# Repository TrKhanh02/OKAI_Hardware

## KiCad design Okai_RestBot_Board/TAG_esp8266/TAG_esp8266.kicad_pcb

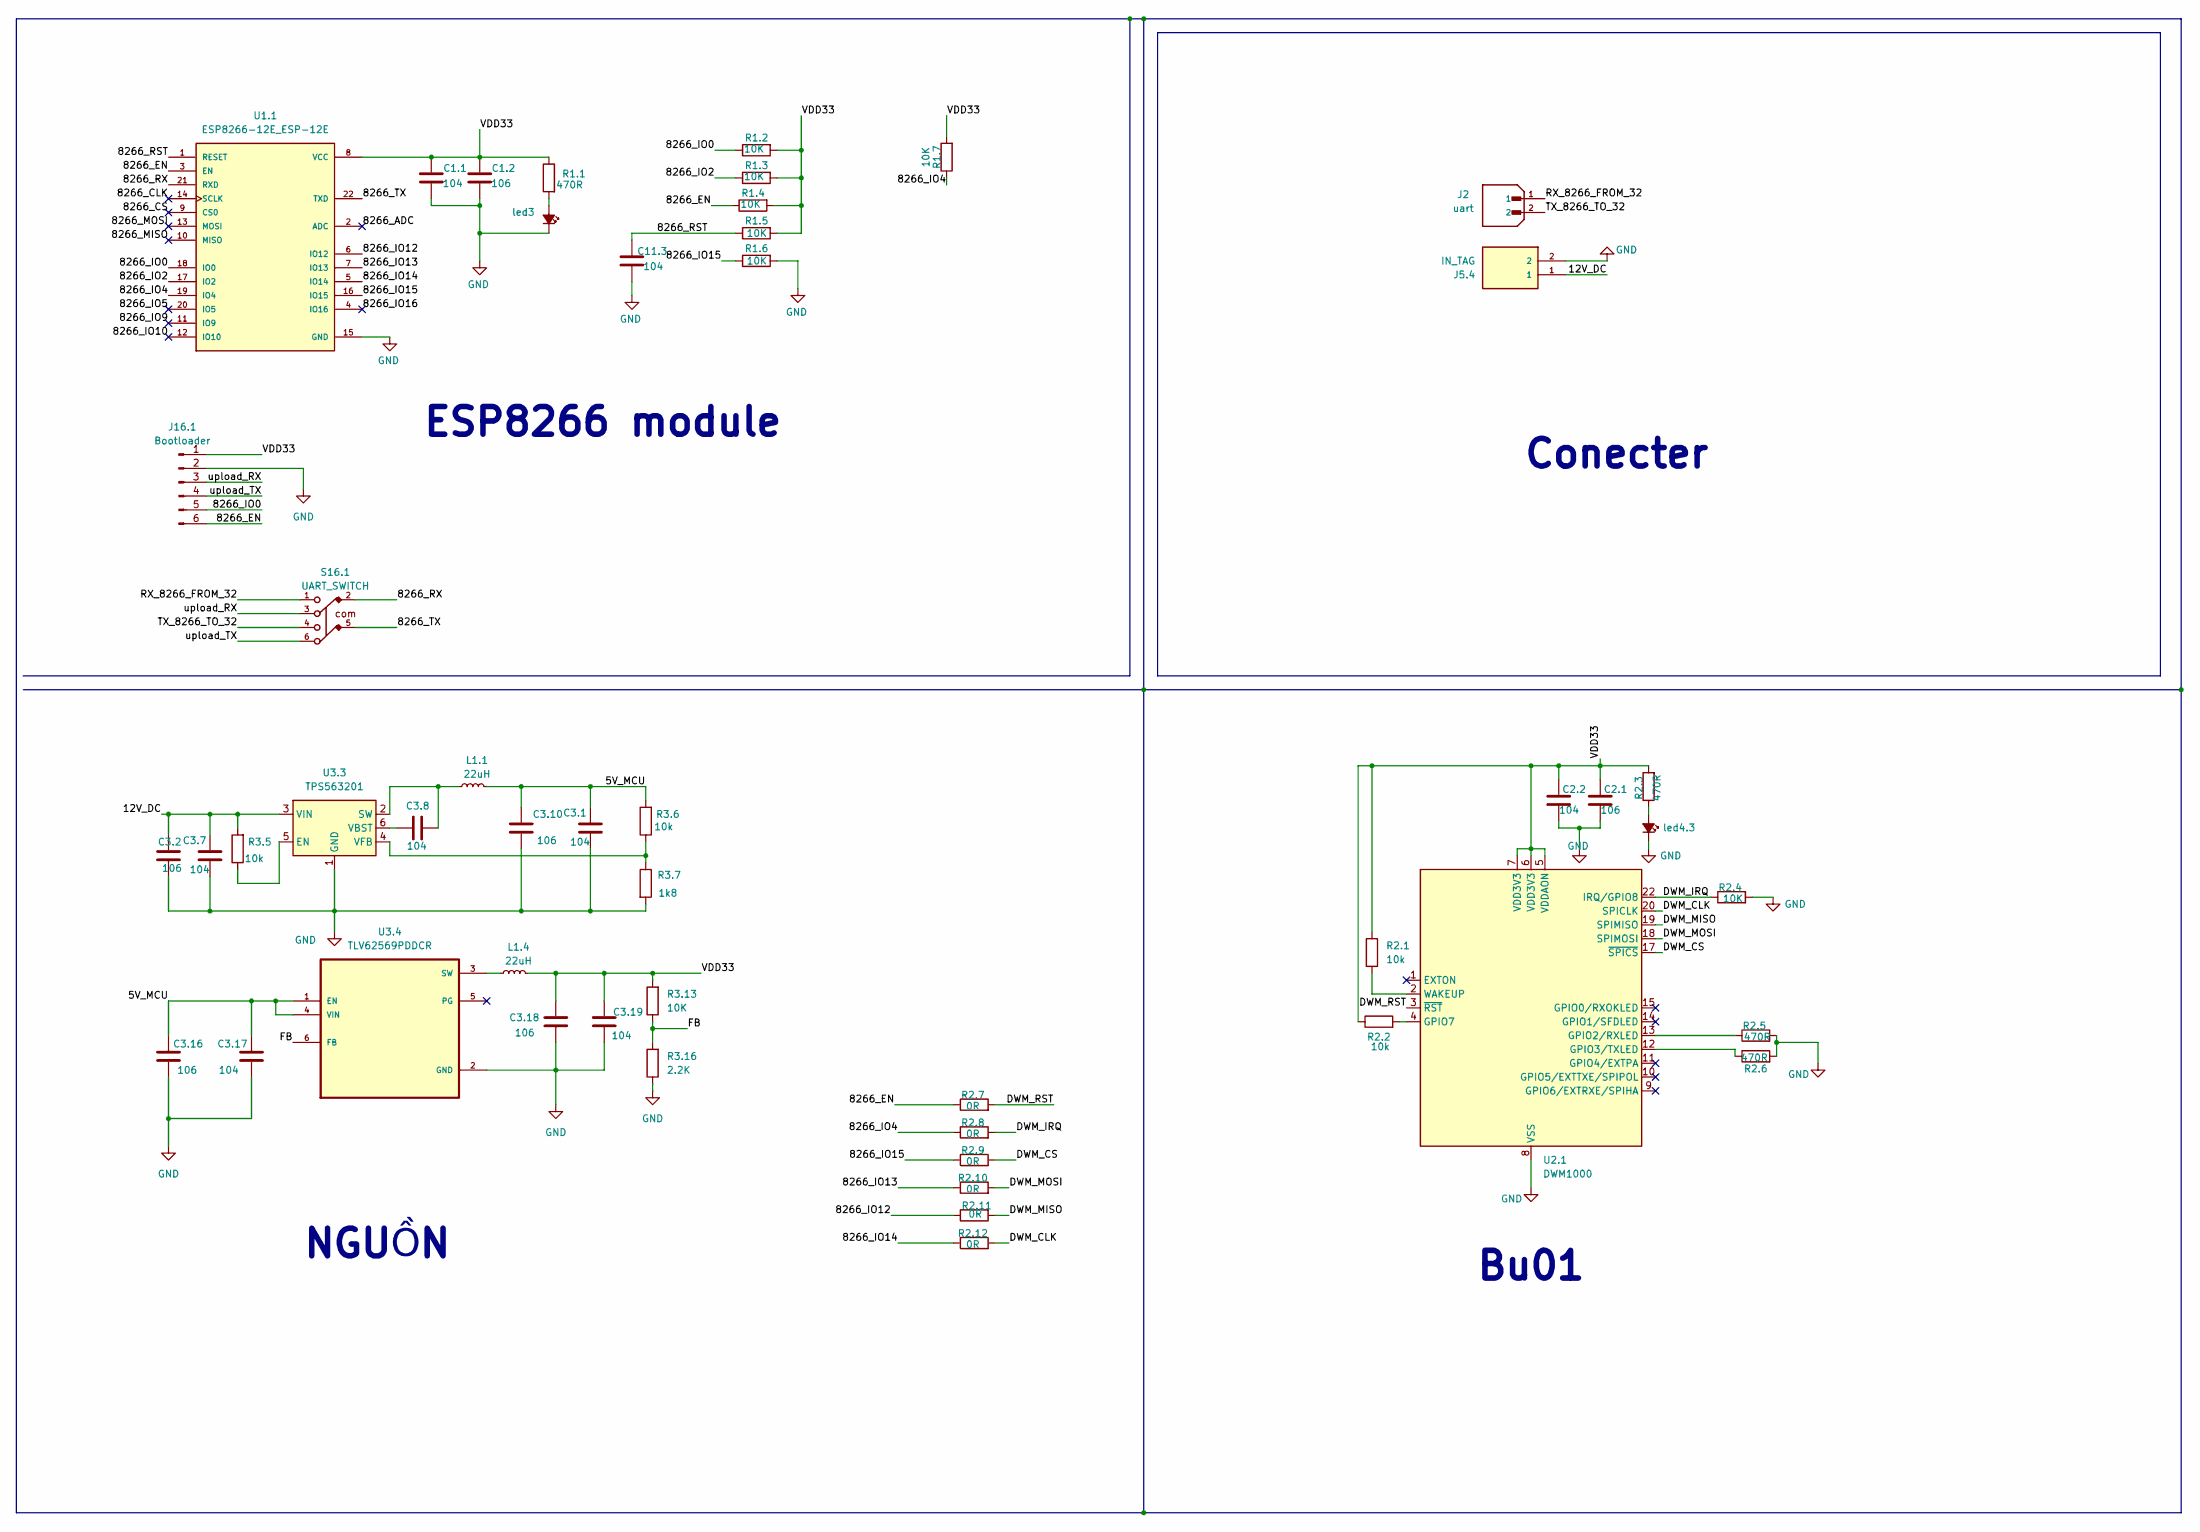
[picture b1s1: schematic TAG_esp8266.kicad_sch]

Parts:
C1.1, C2.2, C11.3: 104; C_0805_2012Metric_Pad1.18x1.45mm_HandSolder
C1.2, C2.1: 106; C_0805_2012Metric_Pad1.18x1.45mm_HandSolder
C3.1, C3.7, C3.8, C3.17, C3.19: 104; C_0805_2012Metric
C3.2, C3.10, C3.16, C3.18: 106; C_0805_2012Metric
J2: uart; JST_B2B-XH-A_LF__SN_; PARTREV N/A
J5.4: IN_TAG; CUI_TBP04R1-500-02BE; PARTREV 1.0
J16.1: Bootloader; PinSocket_1x06_P2.54mm_Vertical
L1.1, L1.4: 22uH; L_Ferrocore_DLG-0705
R1.1, R2.3, R2.5, R2.6: 470R; R_0805_2012Metric_Pad1.20x1.40mm_HandSolder
R1.2, R1.3, R1.4, R1.5, R1.6, R1.7, R2.4: 10K; R_0805_2012Metric_Pad1.20x1.40mm_HandSolder
R2.1, R2.2: 10k; R_0805_2012Metric_Pad1.20x1.40mm_HandSolder
R2.7, R2.8, R2.9, R2.10, R2.11, R2.12: 0R; R_0805_2012Metric_Pad1.20x1.40mm_HandSolder
R3.5, R3.6: 10k; R_0805_2012Metric
R3.7: 1k8; R_0805_2012Metric
R3.13: 10K; R_0805_2012Metric
R3.16: 2.2K; R_0805_2012Metric
S16.1: UART_SWITCH; 452406020024
U1.1: ESP8266-12E_ESP-12E; XCVR_ESP8266-12E_ESP-12E
U2.1: DWM1000
U3.3: TPS563201; SOT-23-6
U3.4: TLV62569PDDCR; SOT95P280X110-6N
led3, led4.3: LED_Small_Filled; LED_0805_2012Metric_Pad1.15x1.40mm_HandSolder

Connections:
/5V_MCU: C3.1.1, C3.10.1, C3.16.1, C3.17.1, L1.1.1, R3.6.2, U3.4.1 (EN), U3.4.4 (VIN)
/12V_DC: C3.2.1, C3.7.1, J5.4.1, R3.5.2, U3.3.3 (VIN)
/8266_ADC: U1.1.2 (ADC)
/8266_CLK: U1.1.14 (SCLK)
/8266_CS: U1.1.9 (CS0)
/8266_EN: J16.1.6, R1.4.1, R2.7.1, U1.1.3 (EN)
/8266_IO0: J16.1.5, R1.2.1, U1.1.18 (IO0)
/8266_IO2: R1.3.1, U1.1.17 (IO2)
/8266_IO4: R1.7.1, R2.8.1, U1.1.19 (IO4)
/8266_IO5: U1.1.20 (IO5)
/8266_IO9: U1.1.11 (IO9)
/8266_IO10: U1.1.12 (IO10)
/8266_IO12: R2.11.1, U1.1.6 (IO12)
/8266_IO13: R2.10.1, U1.1.7 (IO13)
/8266_IO14: R2.12.1, U1.1.5 (IO14)
/8266_IO15: R1.6.1, R2.9.1, U1.1.16 (IO15)
/8266_IO16: U1.1.4 (IO16)
/8266_MISO: U1.1.10 (MISO)
/8266_MOSI: U1.1.13 (MOSI)
/8266_RST: C11.3.1, R1.5.1, U1.1.1 (RESET)
/8266_RX: S16.1.2, U1.1.21 (RXD)
/8266_TX: S16.1.5, U1.1.22 (TXD)
/DWM_CLK: R2.12.2, U2.1.20 (SPICLK)
/DWM_CS: R2.9.2, U2.1.17 (~SPICS)
/DWM_IRQ: R2.4.1, R2.8.2, U2.1.22 (IRQ/GPIO8)
/DWM_MISO: R2.11.2, U2.1.19 (SPIMISO)
/DWM_MOSI: R2.10.2, U2.1.18 (SPIMOSI)
/DWM_RST: R2.7.2, U2.1.3 (~RST)
/FB: R3.13.1, R3.16.2, U3.4.6 (FB)
/RX_8266_FROM_32: J2.1, S16.1.1
/TX_8266_TO_32: J2.2, S16.1.4
/VDD33: C1.1.1, C1.2.1, C2.1.1, C2.2.1, C3.18.1, C3.19.1, J16.1.1, L1.4.1, R1.1.1, R1.2.2, R1.3.2, R1.4.2, R1.5.2, R1.7.2, R2.1.1, R2.2.1, R2.3.2, R3.13.2, U1.1.8 (VCC), U2.1.5 (VDDAON), U2.1.6 (VDD3V3), U2.1.7 (VDD3V3)
/upload_RX: J16.1.3, S16.1.3
/upload_TX: J16.1.4, S16.1.6
GND: C1.1.2, C1.2.2, C2.1.2, C2.2.2, C3.1.2, C3.2.2, C3.7.2, C3.10.2, C3.16.2, C3.17.2, C3.18.2, C3.19.2, C11.3.2, J5.4.2, J16.1.2, R1.6.2, R2.4.2, R2.5.2, R2.6.2, R3.7.2, R3.16.1, U1.1.15 (GND), U2.1.8 (VSS), U2.1.16 (VSS), U2.1.21 (VSS), U2.1.23 (VSS), U2.1.24 (VSS), U3.3.1 (GND), U3.4.2 (GND), led3.1 (K), led4.3.1 (K)
unnamed: R2.5.1, U2.1.13 (GPIO2/RXLED)
unnamed: R2.6.1, U2.1.12 (GPIO3/TXLED)
unnamed: R2.2.2, U2.1.4 (GPIO7)
unnamed: R2.1.2, U2.1.2 (WAKEUP)
unnamed: R3.5.1, U3.3.5 (EN)
unnamed: C3.8.2, L1.1.2, U3.3.2 (SW)
unnamed: C3.8.1, U3.3.6 (VBST)
unnamed: R3.6.1, R3.7.1, U3.3.4 (VFB)
unnamed: L1.4.2, U3.4.3 (SW)
unnamed: R1.1.2, led3.2 (A)
unnamed: R2.3.1, led4.3.2 (A)

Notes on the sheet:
NGUỒN
ESP8266 module
Bu01
Conecter

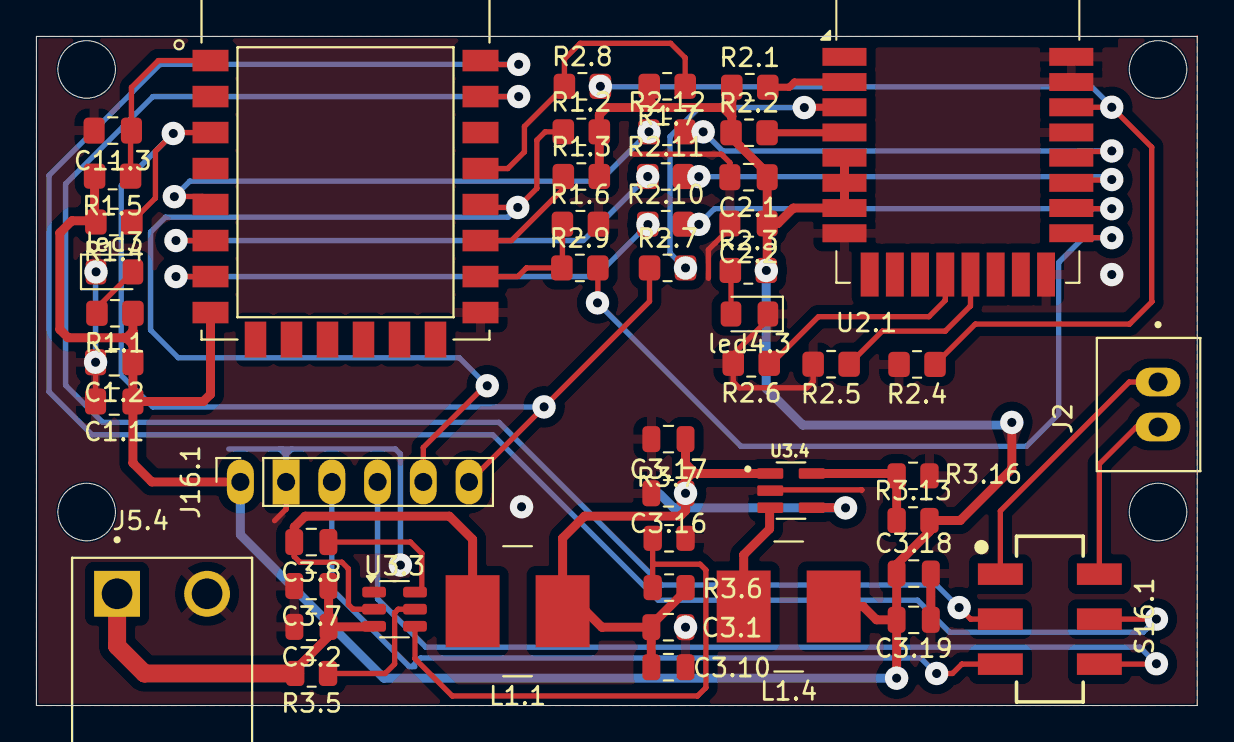
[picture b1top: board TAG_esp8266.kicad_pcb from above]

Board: 2 copper layers, 64.5 x 37.2 mm, 50 parts (0 on the bottom side), 37 nets.

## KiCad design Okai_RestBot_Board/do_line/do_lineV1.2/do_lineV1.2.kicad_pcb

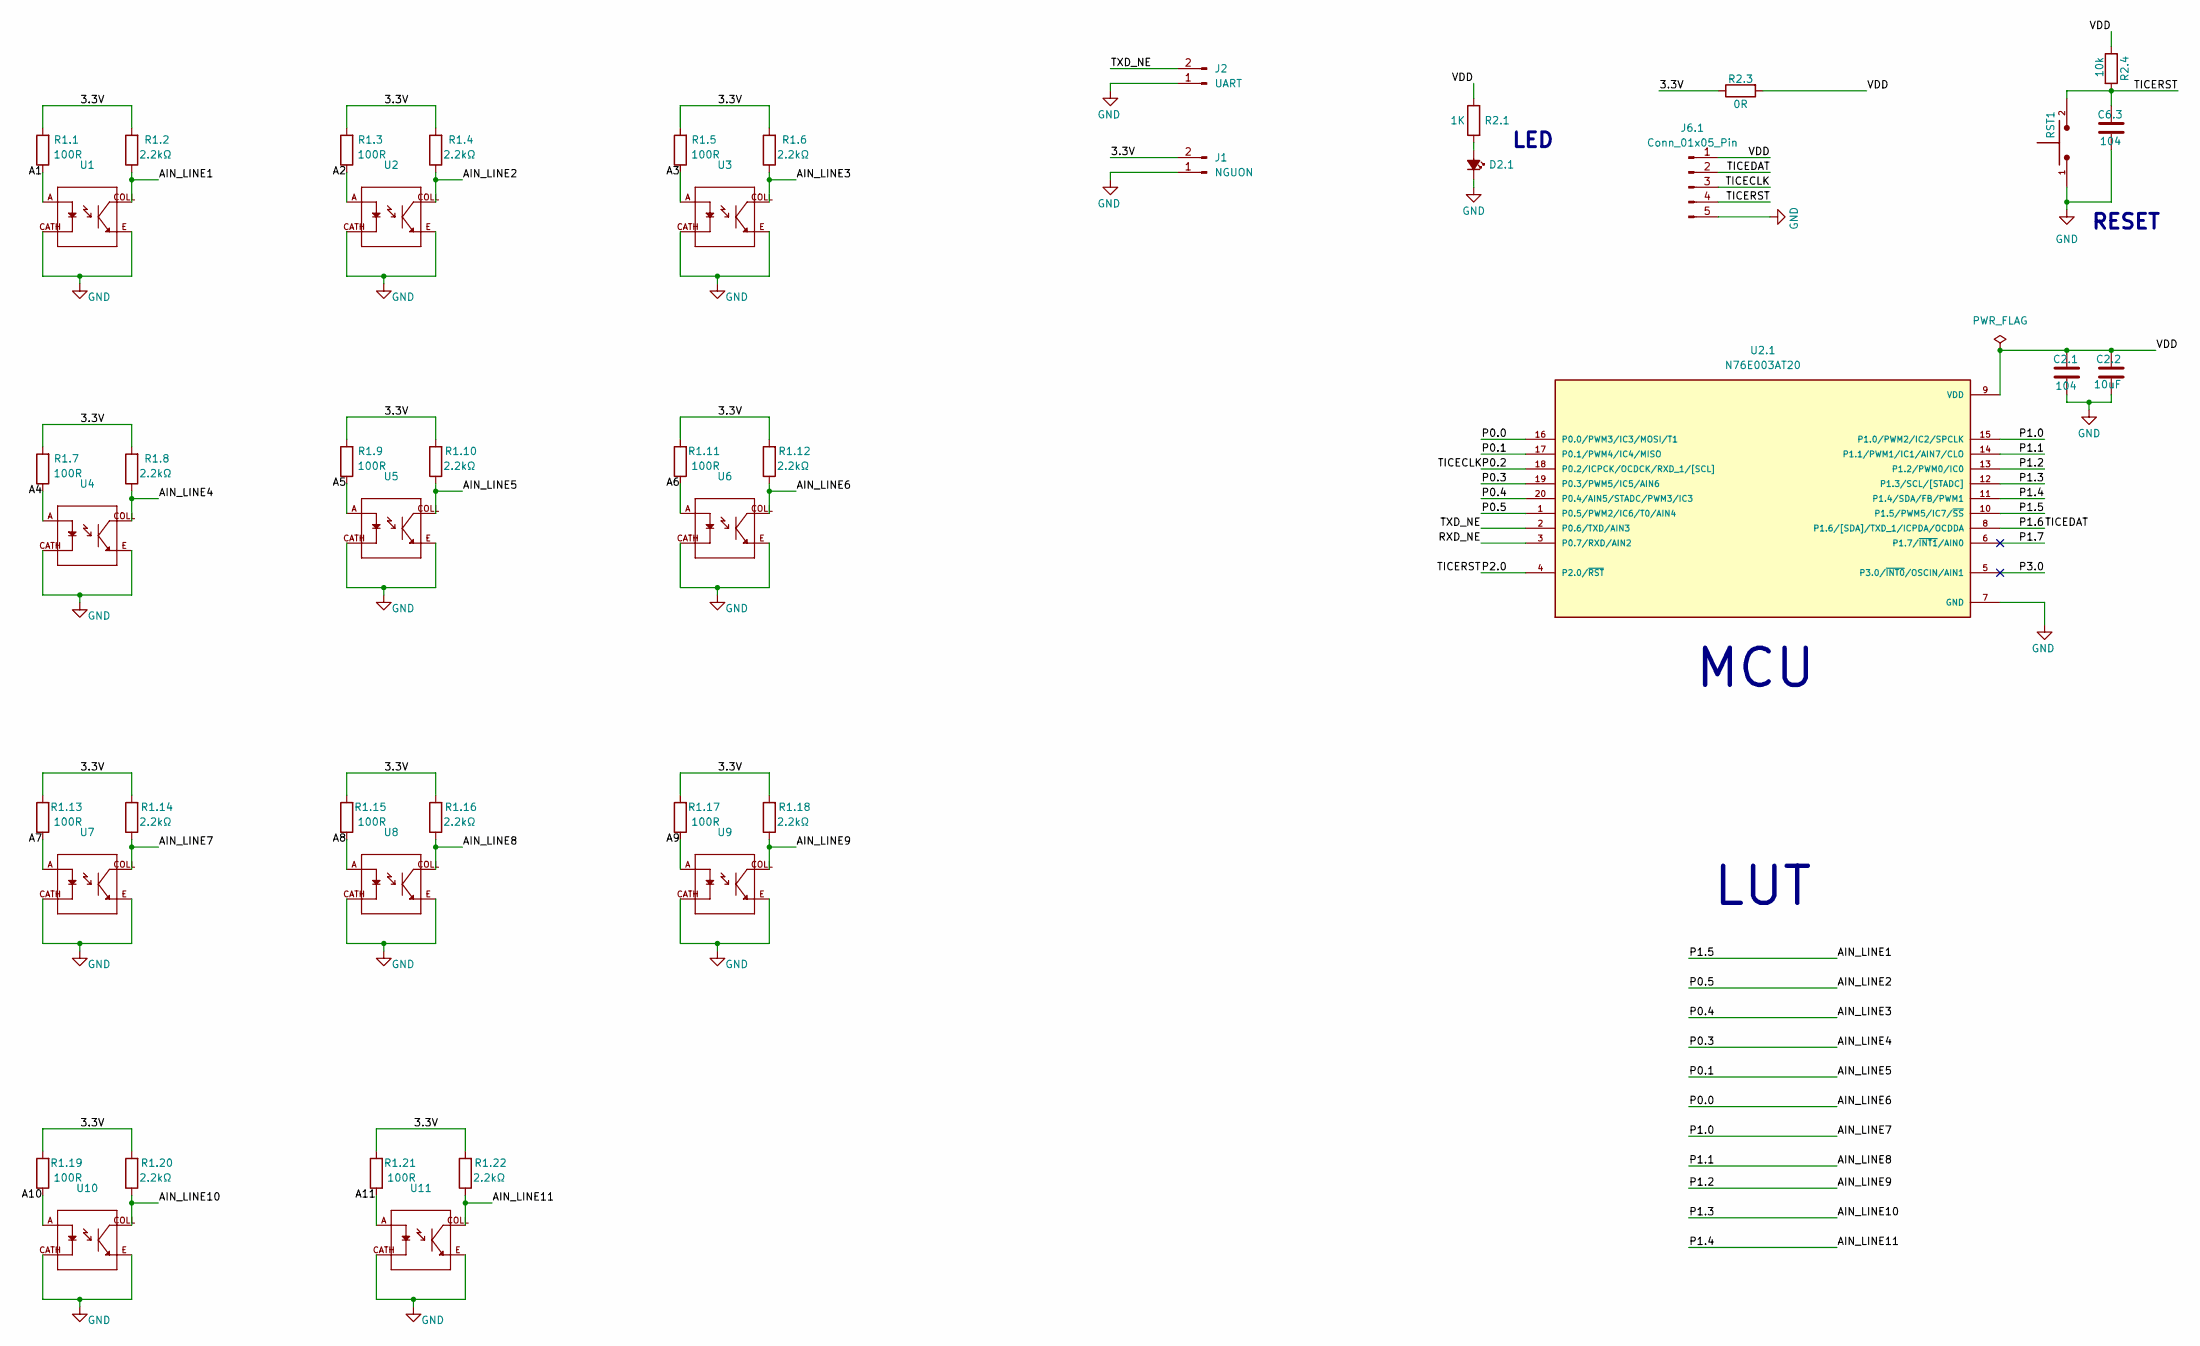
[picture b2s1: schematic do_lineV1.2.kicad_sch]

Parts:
C2.1, C6.3: 104; C_0805_2012Metric_Pad1.18x1.45mm_HandSolder
C2.2: 10uF; C_0805_2012Metric_Pad1.18x1.45mm_HandSolder
D2.1: LED_Small_Filled; LED_0805_2012Metric_Pad1.15x1.40mm_HandSolder
J1: NGUON; PinHeader_1x02_P2.54mm_Vertical
J2: UART; PinHeader_1x02_P2.54mm_Vertical
J6.1: Conn_01x05_Pin; PinHeader_1x05_P2.54mm_Vertical
R1.1, R1.3, R1.5, R1.7, R1.9, R1.11, R1.13, R1.15, R1.17, R1.19, R1.21: 100R; R_0805_2012Metric
R1.2, R1.4, R1.6, R1.8, R1.10, R1.12, R1.14, R1.16, R1.18, R1.20, R1.22: 2.2kΩ; R_0805_2012Metric
R2.1: 1K; R_0805_2012Metric_Pad1.20x1.40mm_HandSolder
R2.3: 0R; R_0805_2012Metric_Pad1.20x1.40mm_HandSolder
R2.4: 10k; R_0805_2012Metric_Pad1.20x1.40mm_HandSolder
RST1: TS10-63-26-BE-250-SMT-TR; SW_TS10-63-26-BE-250-SMT-TR; PARTREV 1.0
U1, U2, U3, U4, U5, U6, U7, U8, U9, U10, U11: Customdoline
U2.1: N76E003AT20; SOP65P640X120-20N; PARTREV 1.04

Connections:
/3.3V: J1.2, R1.1.2, R1.2.2, R1.3.2, R1.4.2, R1.5.2, R1.6.2, R1.7.2, R1.8.2, R1.9.2, R1.10.2, R1.11.2, R1.12.2, R1.13.2, R1.14.2, R1.15.2, R1.16.2, R1.17.2, R1.18.2, R1.19.2, R1.20.2, R1.21.2, R1.22.2, R2.3.1
/A1: R1.1.1, U1.A
/A2: R1.3.1, U2.A
/A3: R1.5.1, U3.A
/A4: R1.7.1, U4.A
/A5: R1.9.1, U5.A
/A6: R1.11.1, U6.A
/A7: R1.13.1, U7.A
/A8: R1.15.1, U8.A
/A9: R1.17.1, U9.A
/A10: R1.19.1, U10.A
/A11: R1.21.1, U11.A
/AIN_LINE1: R1.2.1, U1.COLL, U2.1.10 (P1.5/PWM5/IC7/~SS)
/AIN_LINE2: R1.4.1, U2.COLL, U2.1.1 (P0.5/PWM2/IC6/T0/AIN4)
/AIN_LINE3: R1.6.1, U2.1.20 (P0.4/AIN5/STADC/PWM3/IC3), U3.COLL
/AIN_LINE4: R1.8.1, U2.1.19 (P0.3/PWM5/IC5/AIN6), U4.COLL
/AIN_LINE5: R1.10.1, U2.1.17 (P0.1/PWM4/IC4/MISO), U5.COLL
/AIN_LINE6: R1.12.1, U2.1.16 (P0.0/PWM3/IC3/MOSI/T1), U6.COLL
/AIN_LINE7: R1.14.1, U2.1.15 (P1.0/PWM2/IC2/SPCLK), U7.COLL
/AIN_LINE8: R1.16.1, U2.1.14 (P1.1/PWM1/IC1/AIN7/CLO), U8.COLL
/AIN_LINE9: R1.18.1, U2.1.13 (P1.2/PWM0/IC0), U9.COLL
/AIN_LINE10: R1.20.1, U2.1.12 (P1.3/SCL/[STADC]), U10.COLL
/AIN_LINE11: R1.22.1, U2.1.11 (P1.4/SDA/FB/PWM1), U11.COLL
/P0.2: J6.1.3, U2.1.18 (P0.2/ICPCK/OCDCK/RXD_1/[SCL])
/P1.6: J6.1.2, U2.1.8 (P1.6/[SDA]/TXD_1/ICPDA/OCDDA)
/P1.7: U2.1.6 (P1.7/~INT1/AIN0)
/P2.0: C6.3.1, J6.1.4, R2.4.2, RST1.2, U2.1.4 (P2.0/~RST)
/P3.0: U2.1.5 (P3.0/~INT0/OSCIN/AIN1)
/RXD_NE: U2.1.3 (P0.7/RXD/AIN2)
/TXD_NE: J2.2, U2.1.2 (P0.6/TXD/AIN3)
/VDD: C2.1.1, C2.2.1, J6.1.1, R2.1.1, R2.3.2, R2.4.1, U2.1.9 (VDD)
GND: C2.1.2, C2.2.2, C6.3.2, D2.1.1 (K), J1.1, J2.1, J6.1.5, RST1.1, U1.CATH, U1.E, U2.CATH, U2.E, U2.1.7 (GND), U3.CATH, U3.E, U4.CATH, U4.E, U5.CATH, U5.E, U6.CATH, U6.E, U7.CATH, U7.E, U8.CATH, U8.E, U9.CATH, U9.E, U10.CATH, U10.E, U11.CATH, U11.E
unnamed: D2.1.2 (A), R2.1.2

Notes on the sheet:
MCU
LED
LUT
RESET

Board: 2 copper layers, 45 parts (0 on the bottom side), 30 nets, no tracks yet.
